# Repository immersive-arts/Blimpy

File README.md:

# blimpy

## Connectors

All:

- Type: JST PH RA (S2B-PH-SM4)
- Pitch: 2.00mm (0.079in)
- Current: 2 A
- Wire Size: 32 to 24 AWG

## Cables

Actors:

- Wire Gauge: 26
- Cross Section: 0.129mm2
- Max Current: 2.2A

Battery:

- Wire Gauge: 24
- Cross Section: 0.205mm2
- Max Current: 3.5A

## Board Settings

Trace Widths for 1oz Copper:

- Logic: 0.2mm, ~8mil (.8A)
- Power: 0.4mm, 15mil (1A)
- Actors: 0.8mm, 30mil (2A)
- Battery: 1.2mm, 60mil (3A)

Text Size: Vector, 0.6, 15%

Manufacturing Requirements:

- Min Trace: 6mil
- Min Space: 6mil
- Min Hole: 0.3mm

## Assemblies

We might want to consider ordering ready made cable assemblies:

- https://www.adafruit.com/category/598
- https://www.fabrimex.com/products/cable-assembly.html

## Tools

- Wire Cutter
- JST Crimp Tool

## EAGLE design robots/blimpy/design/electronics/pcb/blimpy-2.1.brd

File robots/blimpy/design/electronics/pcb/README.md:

# Blimpy PCB

Version 2.1 with step-up voltage regulator fix

## TODO

- integrate step-up voltage regulator (see blimpy-2.1_fix.pdf, step-up voltage regulator to prevent voltage to drop below 3.3V when large current is drawn from battery) 
- improve battery state of charge estimate (potentially remove U4, measure current and terminal voltage of battery directly, and implement battery charge estimator)

## Connectors

All:

- Type: JST PH RA (S2B-PH-SM4)
- Pitch: 2.00mm (0.079in)
- Current: 2 A
- Wire Size: 32 to 24 AWG

## Cables

Actuators:

- Wire Gauge: 26 (28)
- Cross Section: 0.129mm2 (0.0810mm2)
- Max Current: 2.2A (1.4A)

Battery:

- Wire Gauge: 20
- Cross Section: 0.518mm2
- Max Current: 11A

## Board Settings

Trace Widths for 1oz Copper:

- Logic: 0.2mm, ~8mil (.8A)
- Power: 0.4mm, 15mil (1A)
- Actors: 0.8mm, 30mil (2A)
- Battery: 1.2mm, 60mil (3A)

Text Size: Vector, 0.6, 15%

Manufacturing Requirements:

- Min Trace: 6mil
- Min Space: 6mil
- Min Hole: 0.3mm

## Assemblies

We might want to consider ordering ready made cable assemblies:

- https://www.adafruit.com/category/598
- https://www.fabrimex.com/products/cable-assembly.html

## Required Tools

- JST Crimp Tool

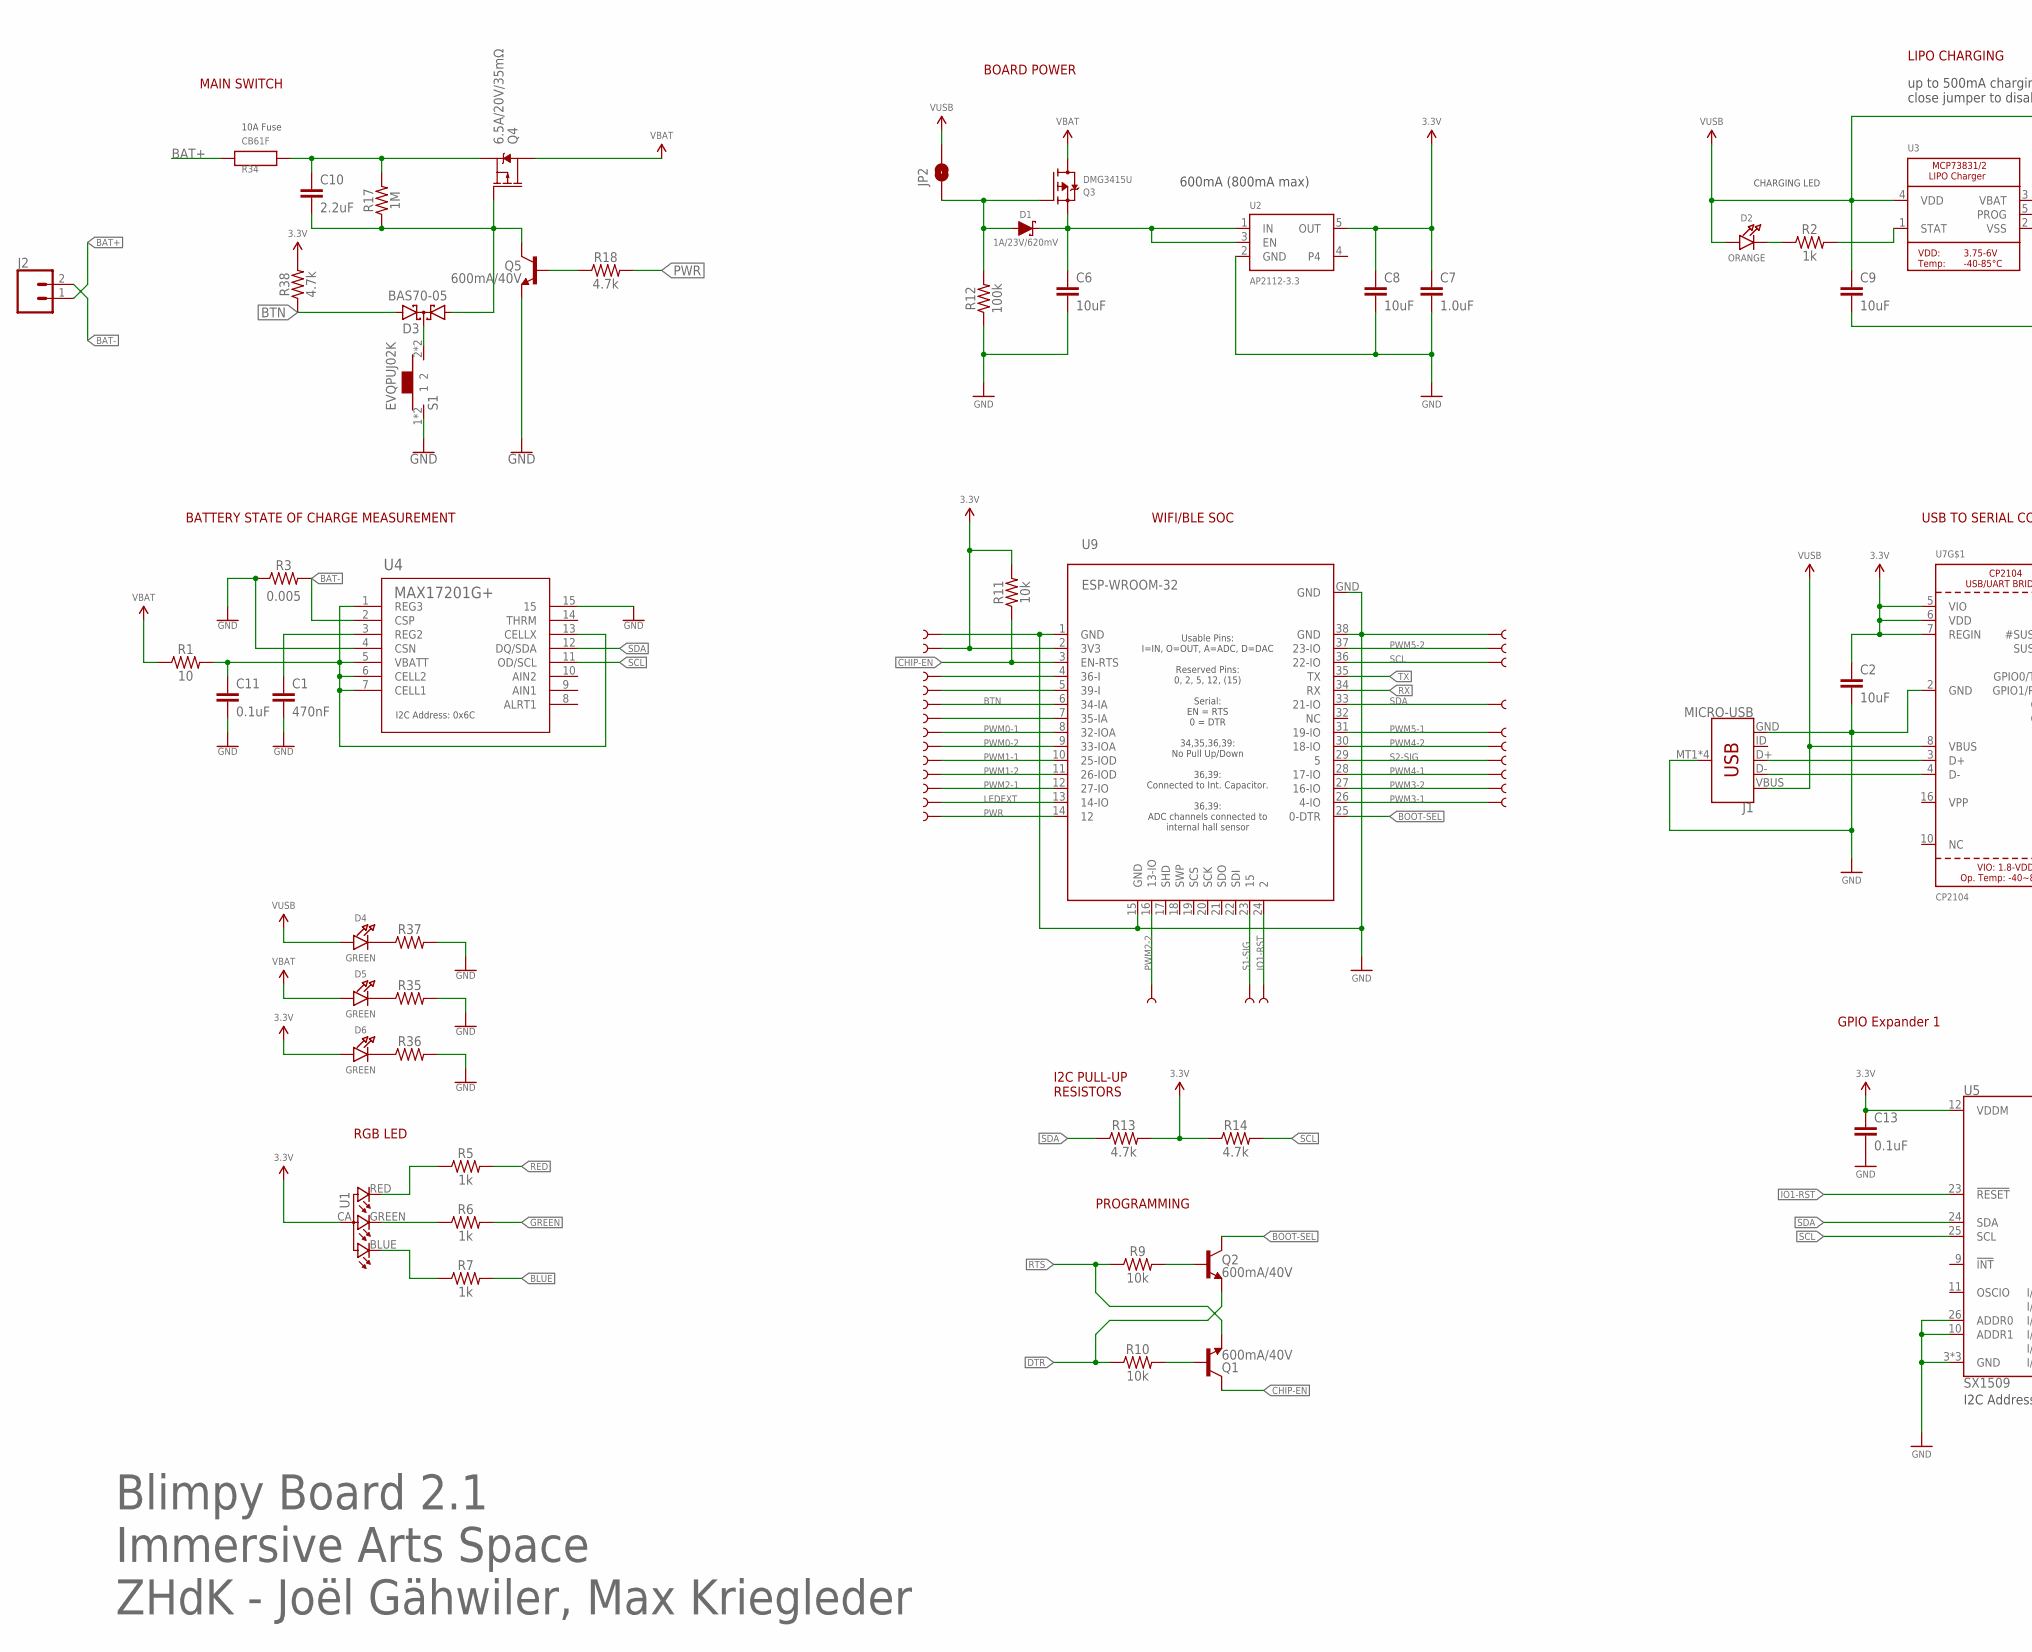
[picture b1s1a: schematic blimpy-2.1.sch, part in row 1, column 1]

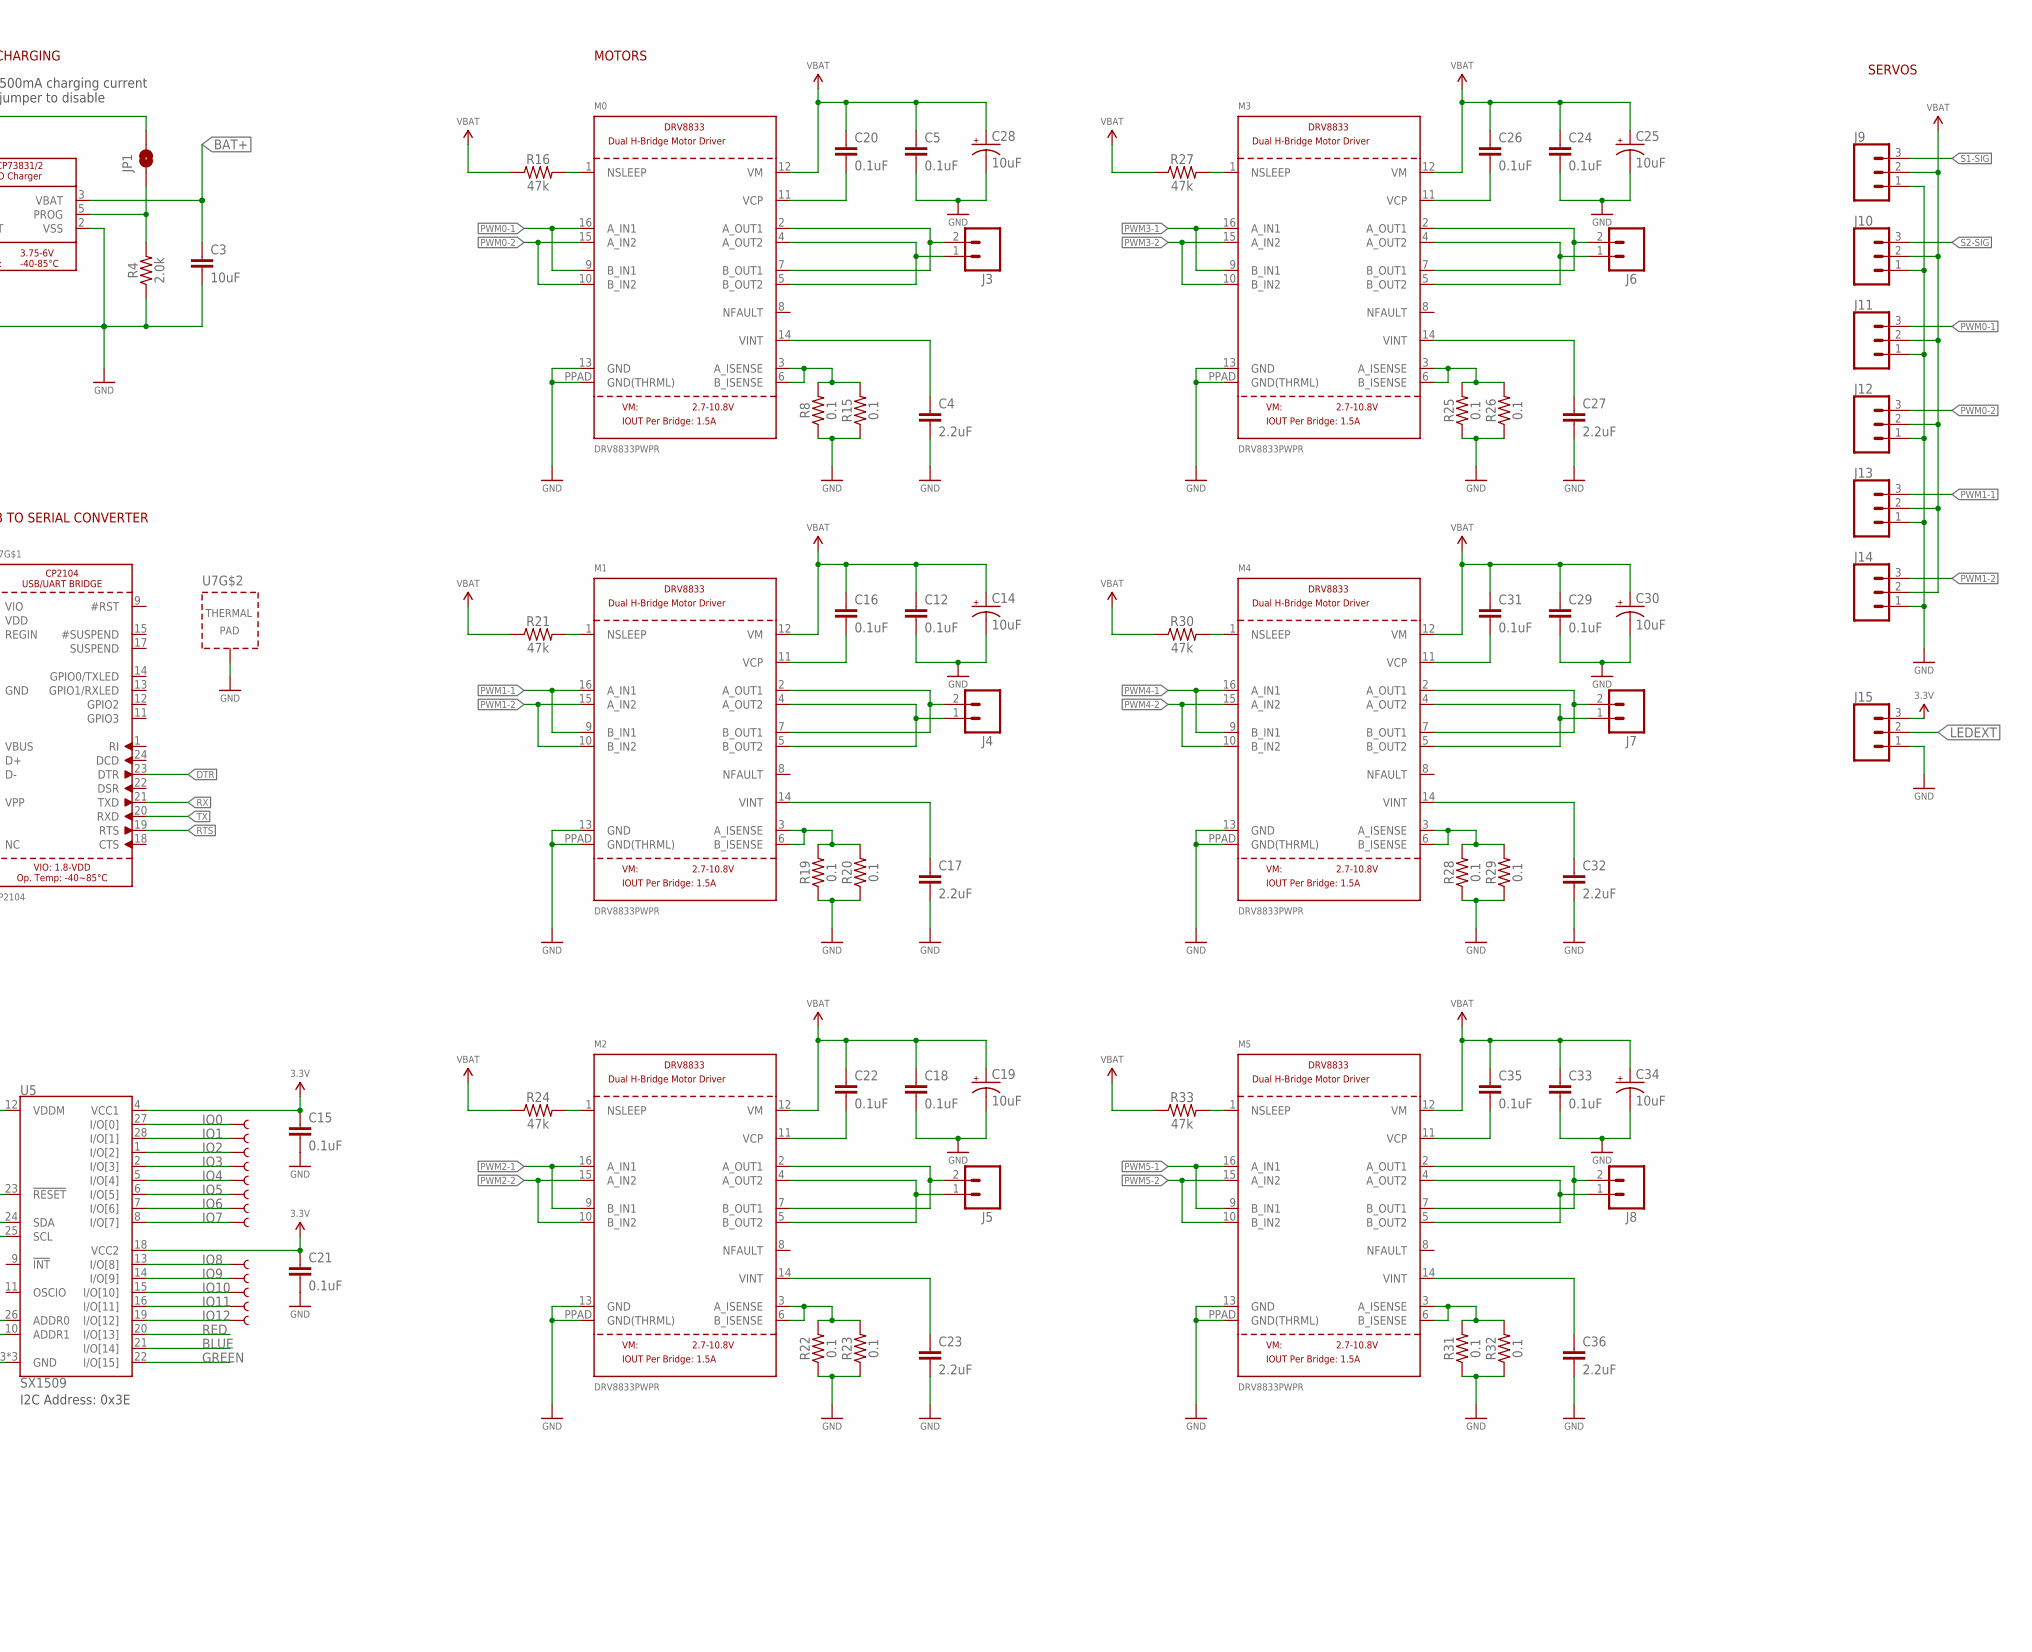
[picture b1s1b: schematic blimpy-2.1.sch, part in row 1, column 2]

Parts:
C1: 470nF; 0603
C2, C3, C6, C8, C9: 10uF; 0603
C4, C10, C17, C23, C27, C32, C36: 2.2uF; 0603
C5, C11, C12, C13, C15, C16, C18, C20, C21, C22, C24, C26, C29, C31, C33, C35: 0.1uF; 0603
C7: 1.0uF; 0603
C14, C19, C25, C28, C30, C34: 10uF; EIA3216
D1: 1A/23V/620mV; SOD-323
D2: ORANGE; CHIPLED_0805_NOOUTLINE
D3: BAS70-05; SOT23
D4, D5, D6: GREEN; CHIPLED_0805_NOOUTLINE
J1: MICRO-USB; USB-MICROB
J2: CONN_02PTH4; 1X02_XTRA_BIG
J3, J4, J5, J6, J7, J8: CONN_02-JST-2MM-SMT; JST-2-SMD
J9, J10, J11, J12, J13, J14, J15: 3-PIN SMD; JST-3-SMD
JP1, JP2: JUMPER-SMT_2_NO_SILK; SMT-JUMPER_2_NO_SILK
M0, M1, M2, M3, M4, M5: DRV8833PWPR; HTSSOP16
Q1, Q2, Q5: 600mA/40V; SOT23-3
Q3: DMG3415U; SOT23-R
Q4: 6.5A/20V/35mΩ; SO08
R1: 10; 0603
R2, R5, R6, R7: 1k; 0603
R3: 0.005; 1206
R4: 2.0k; 0603
R8, R15, R19, R20, R22, R23, R25, R26, R28, R29, R31, R32: 0.1; 1206
R9, R10, R11: 10k; 0603
R12: 100k; 0603
R13, R14, R18, R38: 4.7k; 0603
R16, R21, R24, R27, R30, R33: 47k; 0603
R17: 1M; 0603
R34: CB61F
R35, R36, R37: 0603
S1: EVQPUJ02K
TP1, TP2, TP3, TP4, TP5, TP6, TP7, TP8, TP9, TP10, TP11, TP12, TP13, TP14, TP15, TP16, TP17, TP18, TP19, TP20, TP21, TP22, TP23, TP24, TP25, TP26, TP27, TP28, TP29, TP30, TP31, TP32, TP33, TP34, TP35, TP36, TP37, TP38, TP39: TEST-POINT3; PAD.03X.03
U1: PARTICLE_RGB-LED-CLMVB-FKARGB; PARTICLE_PLCC4-2MM-RGB
U2: AP2112-3.3; SOT23-5
U3: MICROBUILDER_MCP73831/2; MICROBUILDER_SOT23-5
U4: MAX17201G+; 21-0137I_T1433-1_MXM
U5: SX1509; QFN-28
U7: CP2104; QFN24_4MM_SMSC
U9: ESP-WROOM-32

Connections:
3.3V: C2.1, C7.1, C8.1, C13.1, C15.1, C21.1, D6.A, J15.3, R11.2, R13.2, R14.1, R38.2, TP11.P$1, U1.CA (1), U2.5 (OUT), U5.4 (VCC1), U5.12 (VDDM), U5.18 (VCC2), U7.5 (VIO), U7.6 (VDD), U7.7 (REGIN), U9.2 (3V3)
BAT+: C3.1, J2.1, R34.1, U3.3 (VBAT)
BAT-: J2.2, R3.2, U4.2 (CSP)
BLUE: R7.2, U5.21 (I/O[14])
BOOT-SEL: Q2.3 (C), U9.25 (0-DTR)
BTN: D3.2 (A2), R38.1, TP8.P$1, U9.6 (34-IA)
CHIP-EN: Q1.3 (C), R11.1, U9.3 (EN-RTS)
DTR: Q2.2 (E), R10.1, U7.23 (DTR)
GND: C1.2, C2.2, C3.2, C4.2, C5.2, C6.2, C7.2, C8.2, C9.2, C11.2, C12.2, C13.2, C14.-, C15.2, C17.2, C18.2, C19.-, C21.2, C23.2, C24.2, C25.-, C27.2, C28.-, C29.2, C30.-, C32.2, C33.2, C34.-, C36.2, J1.GND, J1.MT1 (SHIELD), J1.MT2 (SHIELD), J1.P$1 (SHIELD), J1.P$2 (SHIELD), J9.1, J10.1, J11.1, J12.1, J13.1, J14.1, J15.1, M0.13 (GND), M0.PPAD (GND(THRML)), M1.13 (GND), M1.PPAD (GND(THRML)), M2.13 (GND), M2.PPAD (GND(THRML)), M3.13 (GND), M3.PPAD (GND(THRML)), M4.13 (GND), M4.PPAD (GND(THRML)), M5.13 (GND), M5.PPAD (GND(THRML)), Q5.2 (E), R3.1, R4.1, R8.1, R12.1, R15.1, R19.1, R20.1, R22.1, R23.1, R25.1, R26.1, R28.1, R29.1, R31.1, R32.1, R35.2, R36.2, R37.2, S1.1, S1.3 (1), TP12.P$1, TP13.P$1, U2.2 (GND), U3.2 (VSS), U4.4 (CSN), U4.15, U5.3 (GND), U5.10 (ADDR1), U5.17 (GND), U5.26 (ADDR0), U5.29 (GND), U7.2 (GND), U7.THERM (TP), U9.1 (GND), U9.15 (GND), U9.38 (GND), U9.GND
GREEN: R6.2, U5.22 (I/O[15])
IO0: TP27.P$1, U5.27 (I/O[0])
IO1: TP28.P$1, U5.28 (I/O[1])
IO1-RST: TP26.P$1, U5.23 (!RESET), U9.24 (2)
IO2: TP29.P$1, U5.1 (I/O[2])
IO3: TP30.P$1, U5.2 (I/O[3])
IO4: TP31.P$1, U5.5 (I/O[4])
IO5: TP32.P$1, U5.6 (I/O[5])
IO6: TP33.P$1, U5.7 (I/O[6])
IO7: TP34.P$1, U5.8 (I/O[7])
IO8: TP35.P$1, U5.13 (I/O[8])
IO9: TP36.P$1, U5.14 (I/O[9])
IO10: TP37.P$1, U5.15 (I/O[10])
IO11: TP38.P$1, U5.16 (I/O[11])
IO12: TP39.P$1, U5.19 (I/O[12])
LEDEXT: J15.2, TP5.P$1, U9.13 (14-IO)
unnamed: D2.C, R2.1
unnamed: J1.D+, U7.3 (D+)
unnamed: R2.2, U3.1 (STAT)
unnamed: JP1.1, R4.2, U3.5 (PROG)
unnamed: M0.1 (NSLEEP), R16.2
unnamed: J1.D-, U7.4 (D-)
unnamed: C6.1, D1.C, Q3.2 (S), U2.1 (IN), U2.3 (EN)
unnamed: C1.1, U4.3 (REG2)
unnamed: R5.1, U1.RED (4)
unnamed: R7.1, U1.BLUE (2)
unnamed: R6.1, U1.GREEN (3)
unnamed: Q1.1 (B), R10.2
unnamed: Q2.1 (B), R9.2
unnamed: M0.3 (A_ISENSE), M0.6 (B_ISENSE), R8.2, R15.2
unnamed: C11.1, R1.2, U4.1 (REG3), U4.5 (VBATT), U4.6 (CELL2), U4.7 (CELL1), U4.13 (CELLX)
unnamed: C10.2, D3.1 (A1), Q4.4 (G), Q5.3 (C), R17.1
unnamed: D4.C, R37.1
unnamed: C10.1, Q4.1 (S), Q4.2 (S), Q4.3 (S), R17.2, R34.2
unnamed: TP9.P$1, U9.5 (39-I)
unnamed: D1.A, JP2.1, Q3.1 (G), R12.2
unnamed: TP7.P$1, U9.7 (35-IA)
unnamed: D3.3 (C), S1.2, S1.4 (2)
unnamed: Q5.1 (B), R18.1
unnamed: J4.1 (2), M1.4 (A_OUT2), M1.5 (B_OUT2)
unnamed: J4.2 (1), M1.2 (A_OUT1), M1.7 (B_OUT1)
unnamed: C17.1, M1.14 (VINT)
unnamed: C16.2, M1.11 (VCP)
unnamed: M1.3 (A_ISENSE), M1.6 (B_ISENSE), R19.2, R20.2
unnamed: M1.1 (NSLEEP), R21.2
unnamed: J6.1 (2), M3.4 (A_OUT2), M3.5 (B_OUT2)
unnamed: J5.1 (2), M2.4 (A_OUT2), M2.5 (B_OUT2)
unnamed: C23.1, M2.14 (VINT)
unnamed: C22.2, M2.11 (VCP)
unnamed: M2.3 (A_ISENSE), M2.6 (B_ISENSE), R22.2, R23.2
unnamed: M2.1 (NSLEEP), R24.2
unnamed: J6.2 (1), M3.2 (A_OUT1), M3.7 (B_OUT1)
unnamed: J3.2 (1), M0.2 (A_OUT1), M0.7 (B_OUT1)
unnamed: J7.1 (2), M4.4 (A_OUT2), M4.5 (B_OUT2)
unnamed: C27.1, M3.14 (VINT)
unnamed: C26.2, M3.11 (VCP)
unnamed: M3.3 (A_ISENSE), M3.6 (B_ISENSE), R25.2, R26.2
unnamed: M3.1 (NSLEEP), R27.2
unnamed: J8.2 (1), M5.2 (A_OUT1), M5.7 (B_OUT1)
unnamed: J7.2 (1), M4.2 (A_OUT1), M4.7 (B_OUT1)
unnamed: C32.1, M4.14 (VINT)
unnamed: C31.2, M4.11 (VCP)
unnamed: M4.3 (A_ISENSE), M4.6 (B_ISENSE), R28.2, R29.2
unnamed: J5.2 (1), M2.2 (A_OUT1), M2.7 (B_OUT1)
unnamed: M4.1 (NSLEEP), R30.2
unnamed: J8.1 (2), M5.4 (A_OUT2), M5.5 (B_OUT2)
unnamed: D6.C, R36.1
unnamed: C36.1, M5.14 (VINT)
unnamed: C35.2, M5.11 (VCP)
unnamed: M5.3 (A_ISENSE), M5.6 (B_ISENSE), R31.2, R32.2
unnamed: M5.1 (NSLEEP), R33.2
unnamed: D5.C, R35.1
unnamed: TP10.P$1, U9.4 (36-I)
unnamed: J3.1 (2), M0.4 (A_OUT2), M0.5 (B_OUT2)
unnamed: C4.1, M0.14 (VINT)
unnamed: C20.2, M0.11 (VCP)
PWM0-1: J11.3, M0.9 (B_IN1), M0.16 (A_IN1), TP1.P$1, U9.8 (32-IOA)
PWM0-2: J12.3, M0.10 (B_IN2), M0.15 (A_IN2), TP2.P$1, U9.9 (33-IOA)
PWM1-1: J13.3, M1.9 (B_IN1), M1.16 (A_IN1), TP3.P$1, U9.10 (25-IOD)
PWM1-2: J14.3, M1.10 (B_IN2), M1.15 (A_IN2), TP6.P$1, U9.11 (26-IOD)
PWM2-1: M2.9 (B_IN1), M2.16 (A_IN1), TP17.P$1, U9.12 (27-IO)
PWM2-2: M2.10 (B_IN2), M2.15 (A_IN2), TP23.P$1, U9.16 (13-IO)
PWM3-1: M3.9 (B_IN1), M3.16 (A_IN1), TP16.P$1, U9.26 (4-IO)
PWM3-2: M3.10 (B_IN2), M3.15 (A_IN2), TP15.P$1, U9.27 (16-IO)
PWM4-1: M4.9 (B_IN1), M4.16 (A_IN1), TP22.P$1, U9.28 (17-IO)
PWM4-2: M4.10 (B_IN2), M4.15 (A_IN2), TP21.P$1, U9.30 (18-IO)
PWM5-1: M5.9 (B_IN1), M5.16 (A_IN1), TP20.P$1, U9.31 (19-IO)
PWM5-2: M5.10 (B_IN2), M5.15 (A_IN2), TP14.P$1, U9.37 (23-IO)
PWR: R18.2, TP4.P$1, U9.14 (12)
RED: R5.2, U5.20 (I/O[13])
RTS: Q1.2 (E), R9.1, U7.19 (RTS)
RX: U7.21 (TXD), U9.34 (RX)
S1-SIG: J9.3, TP24.P$1, U9.23 (15)
S2-SIG: J10.3, TP25.P$1, U9.29 (5)
SCL: R14.2, TP18.P$1, U4.11 (OD/SCL), U5.25 (SCL), U9.36 (22-IO)
SDA: R13.1, TP19.P$1, U4.12 (DQ/SDA), U5.24 (SDA), U9.33 (21-IO)
TX: U7.20 (RXD), U9.35 (TX)
V_BATT: C5.1, C12.1, C14.+, C16.1, C18.1, C19.+, C20.1, C22.1, C24.1, C25.+, C26.1, C28.+, C29.1, C30.+, C31.1, C33.1, C34.+, C35.1, D5.A, J9.2, J10.2, J11.2, J12.2, J13.2, J14.2, M0.12 (VM), M1.12 (VM), M2.12 (VM), M3.12 (VM), M4.12 (VM), M5.12 (VM), Q3.3 (D), Q4.5 (D), Q4.6 (D), Q4.7 (D), Q4.8 (D), R1.1, R16.1, R21.1, R24.1, R27.1, R30.1, R33.1
V_USB: C9.1, D2.A, D4.A, J1.VBUS, JP1.2, JP2.2, U3.4 (VDD), U7.8 (VBUS)

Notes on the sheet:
BOARD POWER
up to 500mA charging current close jumper to disable
USB TO SERIAL CONVERTER
LIPO CHARGING
RGB LED
PROGRAMMING
CHARGING LED
I2C Address: 0x6C
I2C PULL-UP RESISTORS
WIFI/BLE SOC
GPIO Expander 1
600mA (800mA max)
SERVOS
MOTORS
Blimpy Board 2.1 Immersive Arts Space ZHdK - Joël Gähwiler, Max Kriegleder
BATTERY STATE OF CHARGE MEASUREMENT
I2C Address: 0x3E
MAIN SWITCH
10A Fuse

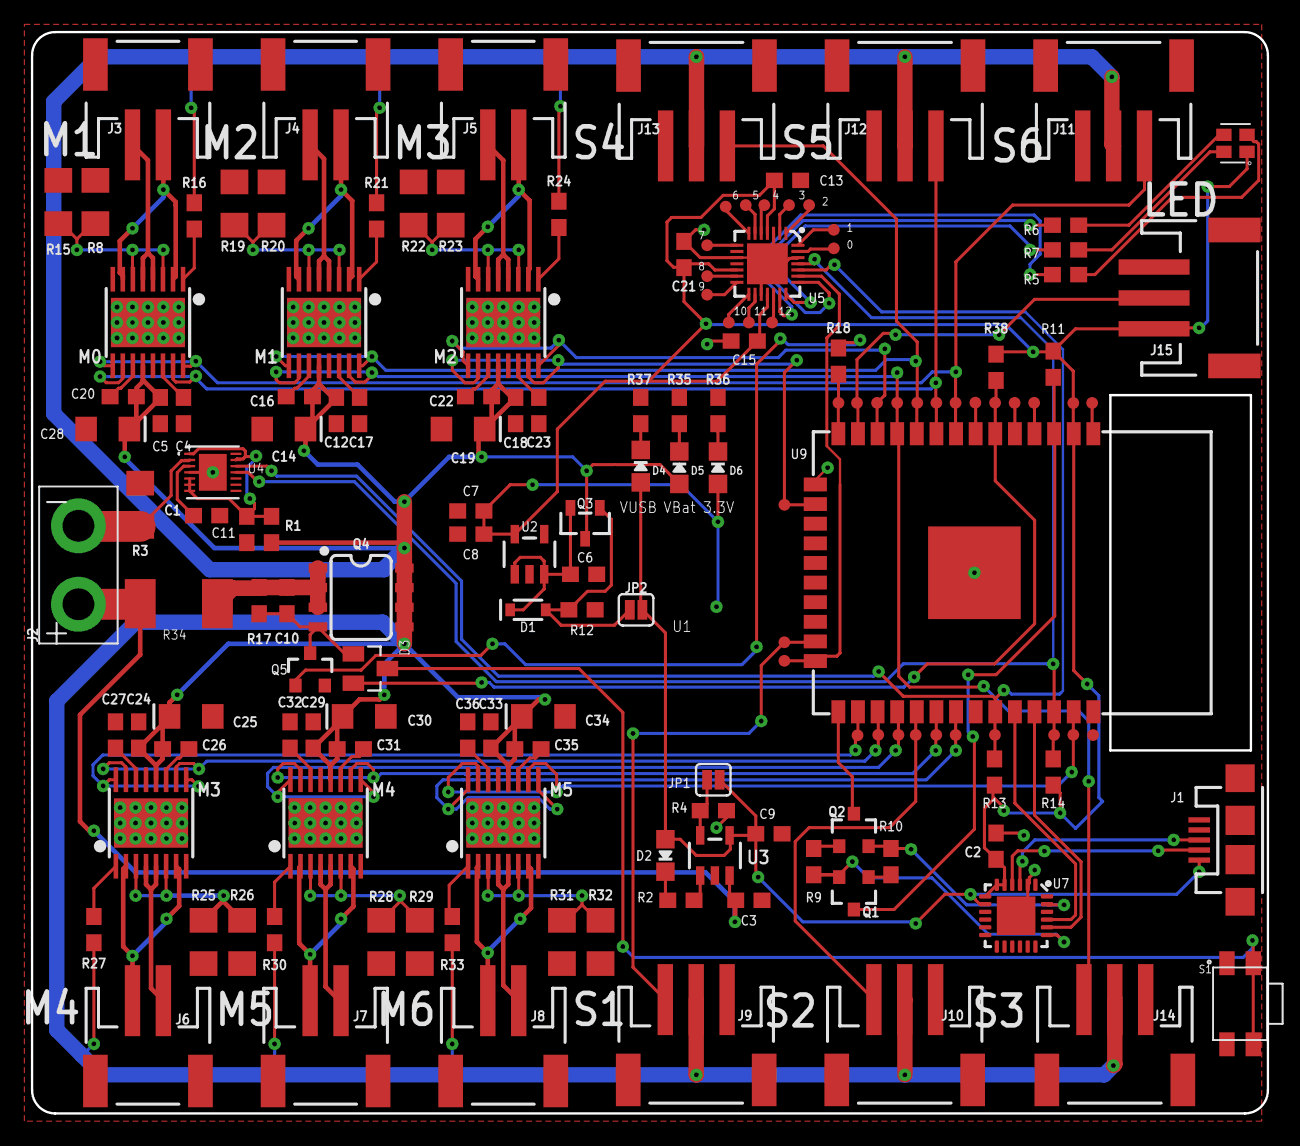
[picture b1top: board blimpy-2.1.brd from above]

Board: 2 copper layers, 80.0 x 70.0 mm, 155 parts (0 on the bottom side), 108 nets.

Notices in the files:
parts and their libraries:
microbuilder: This work is placed in the public domain, and may be freely used for commercial and non-commercial work with the following conditions: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
SparkFun-Capacitors: Licensing: Creative Commons ShareAlike 4.0 International - https://creativecommons.org/licenses/by-sa/4.0
